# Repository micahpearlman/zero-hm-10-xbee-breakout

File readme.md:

## Overview ##

This is an 3.3V XBee breakout of the HM-10 Bluetooth Low Energy Module.

## License ##

Creative Commons Share and Share Alike

## Parts ##

[Order a complete board on Tindie](https://www.tindie.com/products/micahpearlman/zero-xbee-ble/)

[Parts List](https://raw2.github.com/micahpearlman/zero-hm-10-xbee-breakout/master/parts-list.txt)

[Order PCB from Osh Park](https://oshpark.com/shared_projects/l8zO7AMg)

## References ##

[Data Sheet](https://github.com/micahpearlman/zero-hm-10-xbee-breakout/blob/master/docs/hm-10-datasheet.pdf)

HM-10 purchase: http://www.fasttech.com/product/1292002-ti-cc2540-bluetooth-4-0-ble-2540-transparent

Great article: http://letsmakerobots.com/node/38009

## Open HW Reference Designs:

https://github.com/Ladvien/HM-10

https://github.com/SamEA/Bluetooth_Low_Energy

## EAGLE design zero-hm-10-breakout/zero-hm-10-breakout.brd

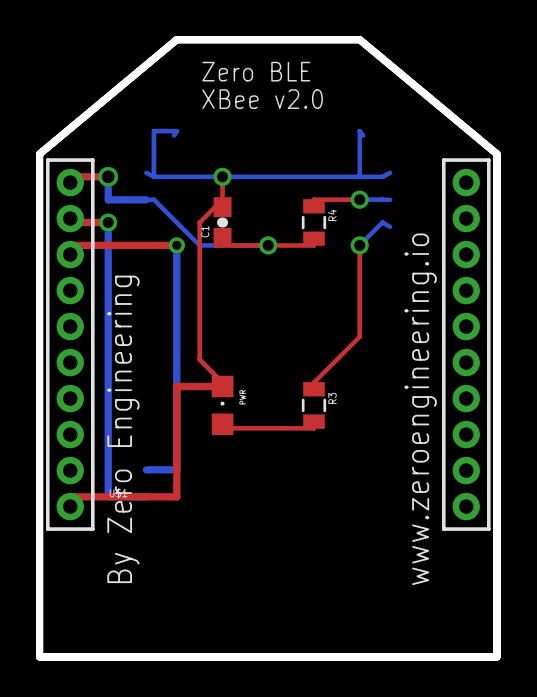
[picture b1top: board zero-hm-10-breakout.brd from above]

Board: 2 copper layers, 25.4 x 34.3 mm, 6 parts (1 on the bottom side), 7 nets.

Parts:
C1: 0.1uF; 0603-CAP
PWR: BLU; CHIPLED_0805
R3, R4: 470R; 0805
U1: HM-10
U$1: XBEE-1B1; XBEE-1

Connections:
GND: C1.2, PWR.C, U1.13, U1.14, U1.21, U1.22, U$1.10
unnamed: PWR.A, R3.2
unnamed: R3.1, U1.24
unnamed: R4.1, U1.23
RX: U1.1, U$1.2
TX: U1.2, U$1.3
VDD: C1.1, R4.2, U1.12, U$1.1

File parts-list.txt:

Partlist

Exported from zero-hm-10-breakout.sch at 2/19/14 10:23 AM

EAGLE Version 6.5.0 Copyright (c) 1988-2013 CadSoft

Assembly variant: 

Part     Value          Device                    Package      Library             Sheet

C1       0.1uF          0.1UF-25V(+80/-20%)(0603) 0603-CAP     SparkFun-Capacitors 1
PWR      BLU            LEDCHIPLED_0805           CHIPLED_0805 adafruit            1
R3       470R           0.3OHM-1/8W-1%(0805)      0805         SparkFun-Resistors  1
R4       470R           0.3OHM-1/8W-1%(0805)      0805         SparkFun-Resistors  1
U$1      XBEE-1B1       XBEE-1B1                  XBEE-1       SparkFun-RF         1
U1       HM-10          HM-10                     HM-10        HM-10_BLE           1

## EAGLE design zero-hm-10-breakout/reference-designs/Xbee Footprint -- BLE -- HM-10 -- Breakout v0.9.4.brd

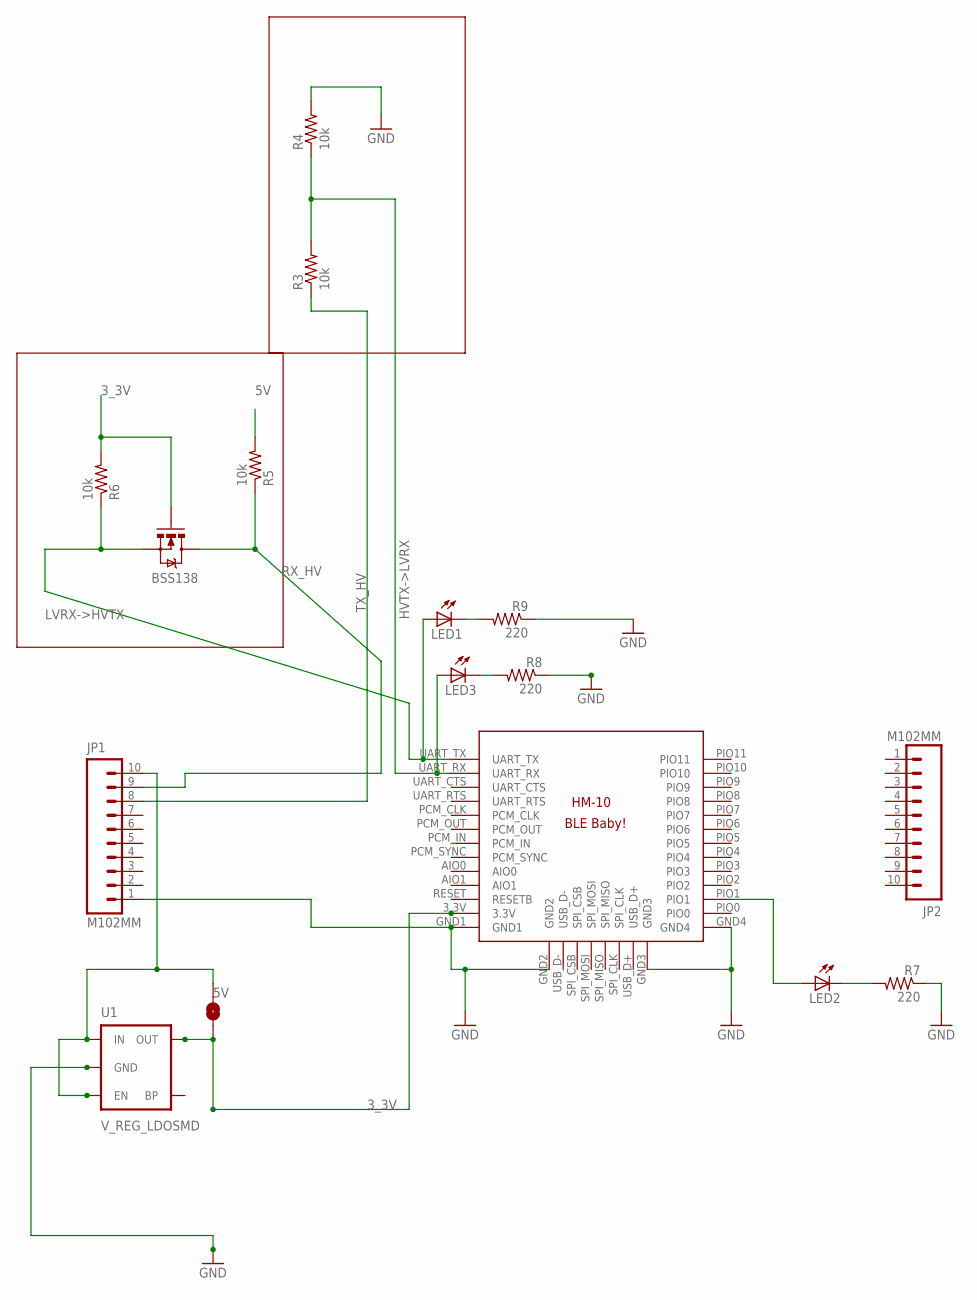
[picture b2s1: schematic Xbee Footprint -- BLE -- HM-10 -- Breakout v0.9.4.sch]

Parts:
BSS138: MOSFET-NCHANNELSMD; SOT23-3
JP1, JP2: M102MM; 1X10-2MM
LED1, LED2, LED3: LED0603; LED-0603
R3, R4, R5, R6: 10k; M0805
R7, R8, R9: 220; M0805
SJ1: SOLDERJUMPERNO; SJ_2S-NO
U1: V_REG_LDOSMD; SOT23-5
U$1: BLE-HM-10

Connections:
3_3V: BSS138.1 (G), R6.2, SJ1.1, U1.5 (OUT), U$1.3.3V
5V: JP1.10, R5.2, SJ1.2, U1.1 (IN), U1.3 (EN)
GND: JP1.1, R4.2, R7.1, R8.1, R9.1, U1.2 (GND), U$1.GND1, U$1.GND2, U$1.GND3, U$1.GND4
HVTX->LVRX: LED3.A, R3.2, R4.1, U$1.UART_RX
LVRX->HVTX: BSS138.2 (S), LED1.A, R6.1, U$1.UART_TX
unnamed: LED2.A, U$1.PIO1
unnamed: LED2.C, R7.2
unnamed: LED1.C, R9.2
unnamed: LED3.C, R8.2
RX_HV: BSS138.3 (D), JP1.9, R5.1
TX_HV: JP1.8, R3.1

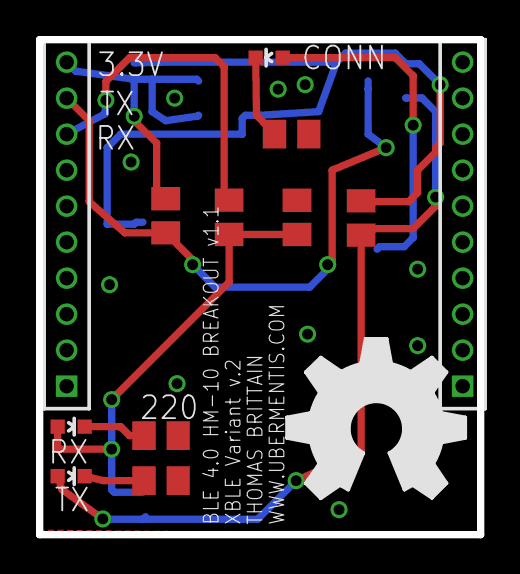
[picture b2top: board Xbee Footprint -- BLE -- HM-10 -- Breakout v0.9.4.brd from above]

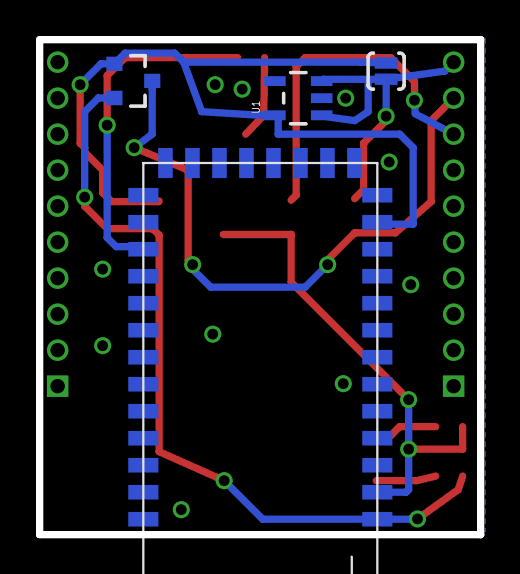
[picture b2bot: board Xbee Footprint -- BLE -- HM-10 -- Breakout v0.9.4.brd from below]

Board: 2 copper layers, 24.5 x 27.5 mm, 17 parts (4 on the bottom side), 11 nets.

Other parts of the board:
U$2: OSHW_FILLX350_NOTEXT

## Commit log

2014-01-31 added readme
2014-02-02 just about todo routing
2014-02-02 first working routing
2014-02-02 good layout
2014-02-02 better board layout
2014-02-02 add text to silk screen
2014-02-02 couple more minor tweaks to text
2014-02-02 final sent to oshpark. tag it and bag it.
2014-02-03 added missing capacitor
2014-02-03 added images
2014-02-03 added images in read me
2014-02-03 added schematic image
2014-02-03 fixed parts list
2014-02-03 parts list
2014-02-19 Fixed RX/TX being backwards and removed the RX/TX LEDs
2014-02-19 updated board and schematic images and parts list
2015-02-03 updated silkscreen
2015-02-03 removed the eagle.epf
2015-02-03 removed unnecessary file
2015-02-15 removed old
2015-02-15 cleaned up directories

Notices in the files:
parts and their libraries:
SparkFun: Licensing: CC v3.0 Share-Alike You are welcome to use this library for commercial purposes.
